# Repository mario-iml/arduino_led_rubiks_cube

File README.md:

# arduino_led_rubiks_cube
Disclaimer: This was in 2019, and we didn't even know about Git yet, so we had to scrape together Code and PCB files from old chats. We take no guarantee that this works and is up-to-date :).

## Description
Arduino based LED Rubik's Cube. 
This Project was made as a High-school Project with two other Students. To achieve this, we had to:
- Design of PCB's encompassing the buttons, LED's and shift registers with EAGLE
- Designing and Printing of the cubes case
- Assembling and Wirering the PCB's and Arduino
- Write the Code in Arduino IDE with C++

## Problems we encountered
- We were all pretty new to Computer Science and Electrical Engineering. We made many mistakes but learned many things in the process.
- We accidentally ordered the wrong type of LEDs (common anode instead of common cathode) for the PCB without realizing it. In the end, we had to desolder some of the LEDs again :(
- There were mistakes in the first version of the PCB design, which caused us to get dangerously close to the deadline due to long delivery times.

## PCB designs
The PCBs were designed with the Eagle software. Design files can be found in the Repo and here are some Screenshots:

## Other Images

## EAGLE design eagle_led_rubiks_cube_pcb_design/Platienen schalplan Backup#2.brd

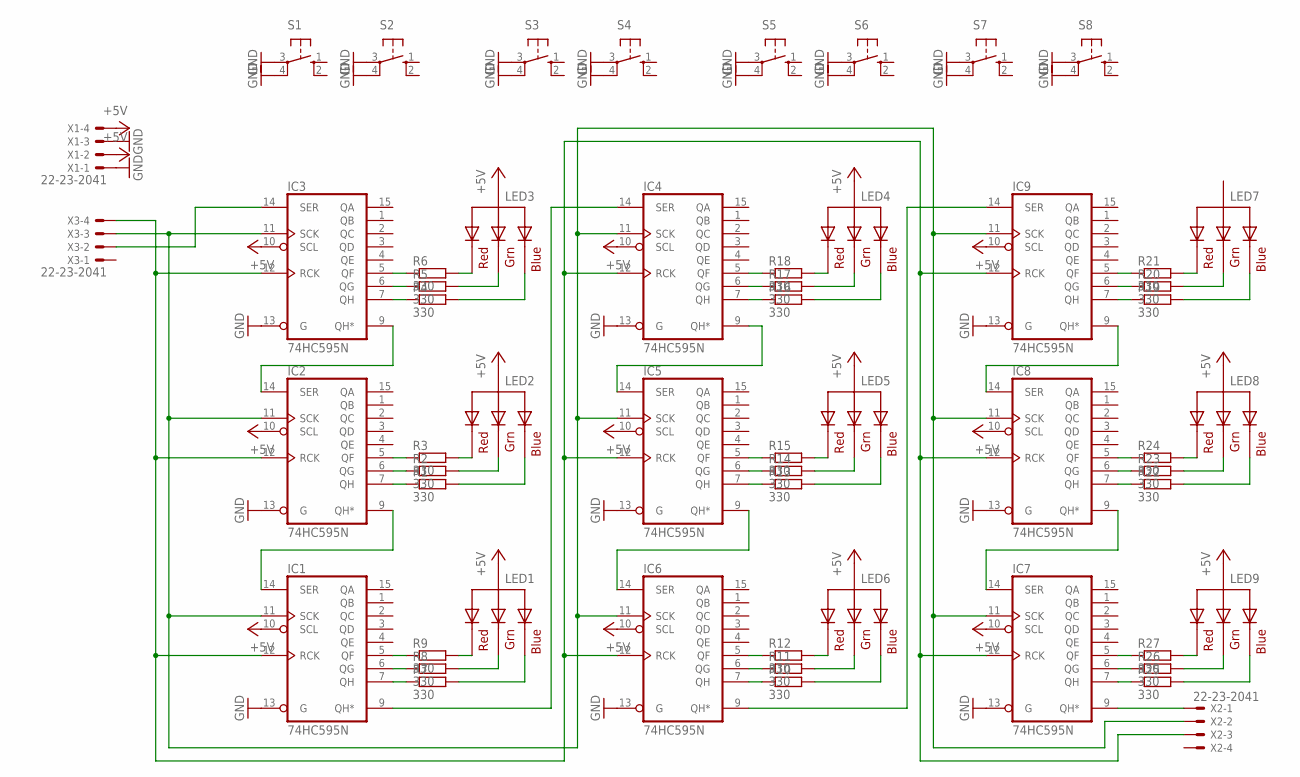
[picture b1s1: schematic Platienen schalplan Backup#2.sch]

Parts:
IC1, IC2, IC3, IC4, IC5, IC6, IC7, IC8, IC9: 74HC595N; DIL16
LED1, LED2, LED3, LED4, LED5, LED6, LED7, LED8, LED9: RGBLED_CA-5MM; LED5MMRGB
R1, R2, R3, R4, R5, R6, R7, R8, R9, R10, R11, R12, R13, R14, R15, R16, R17, R18, R19, R20, R21, R22, R23, R24, R25, R26, R27: 330; 0204/5
S1, S2, S3, S4, S5, S6, S7, S8: 10-XX; B3F-10XX
X1, X2, X3: 22-23-2041

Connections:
+5V: IC1.10 (SCL), IC2.10 (SCL), IC3.10 (SCL), IC4.10 (SCL), IC5.10 (SCL), IC6.10 (SCL), IC7.10 (SCL), IC8.10 (SCL), IC9.10 (SCL), LED1.2 (VCC), LED2.2 (VCC), LED3.2 (VCC), LED4.2 (VCC), LED5.2 (VCC), LED6.2 (VCC), LED8.2 (VCC), LED9.2 (VCC), X1.2, X1.4
GND: IC1.8 (GND), IC1.13 (G), IC2.8 (GND), IC2.13 (G), IC3.8 (GND), IC3.13 (G), IC4.8 (GND), IC4.13 (G), IC5.8 (GND), IC5.13 (G), IC6.8 (GND), IC6.13 (G), IC7.8 (GND), IC7.13 (G), IC8.8 (GND), IC8.13 (G), IC9.8 (GND), IC9.13 (G), S1.3, S1.4 (P1), S2.3, S2.4 (P1), S3.3, S3.4 (P1), S4.3, S4.4 (P1), S5.3, S5.4 (P1), S6.3, S6.4 (P1), S7.3, S7.4 (P1), S8.3, S8.4 (P1), X1.1, X1.3
unnamed: IC3.7 (QH), R4.1
unnamed: IC3.6 (QG), R5.1
unnamed: IC3.5 (QF), R6.1
unnamed: LED5.1 (RED), R15.2
unnamed: LED4.1 (RED), R18.2
unnamed: LED7.1 (RED), R21.2
unnamed: IC2.7 (QH), R1.1
unnamed: IC2.6 (QG), R2.1
unnamed: IC2.5 (QF), R3.1
unnamed: IC1.5 (QF), R9.1
unnamed: IC1.6 (QG), R8.1
unnamed: IC1.7 (QH), R7.1
unnamed: LED7.3 (GREEN), R20.2
unnamed: LED7.4 (BLUE), R19.2
unnamed: LED8.1 (RED), R24.2
unnamed: LED8.3 (GREEN), R23.2
unnamed: LED8.4 (BLUE), R22.2
unnamed: LED9.1 (RED), R27.2
unnamed: IC6.7 (QH), R10.1
unnamed: IC6.6 (QG), R11.1
unnamed: IC6.5 (QF), R12.1
unnamed: LED9.3 (GREEN), R26.2
unnamed: LED9.4 (BLUE), R25.2
unnamed: LED6.1 (RED), R12.2
unnamed: IC5.7 (QH), R13.1
unnamed: IC5.6 (QG), R14.1
unnamed: IC5.5 (QF), R15.1
unnamed: LED6.3 (GREEN), R11.2
unnamed: LED6.4 (BLUE), R10.2
unnamed: LED5.3 (GREEN), R14.2
unnamed: IC4.7 (QH), R16.1
unnamed: IC4.6 (QG), R17.1
unnamed: IC4.5 (QF), R18.1
unnamed: LED5.4 (BLUE), R13.2
unnamed: LED4.3 (GREEN), R17.2
unnamed: LED4.4 (BLUE), R16.2
unnamed: IC9.7 (QH), R19.1
unnamed: IC9.6 (QG), R20.1
unnamed: IC9.5 (QF), R21.1
unnamed: IC8.5 (QF), R24.1
unnamed: IC8.6 (QG), R23.1
unnamed: IC8.7 (QH), R22.1
unnamed: IC7.5 (QF), R27.1
unnamed: IC7.6 (QG), R26.1
unnamed: IC7.7 (QH), R25.1
unnamed: LED2.1 (RED), R3.2
unnamed: LED2.3 (GREEN), R2.2
unnamed: LED2.4 (BLUE), R1.2
unnamed: LED1.1 (RED), R9.2
unnamed: LED1.3 (GREEN), R8.2
unnamed: LED1.4 (BLUE), R7.2
unnamed: LED3.1 (RED), R6.2
unnamed: LED3.3 (GREEN), R5.2
unnamed: IC2.14 (SER), IC3.9 (QH*)
unnamed: IC1.14 (SER), IC2.9 (QH*)
unnamed: IC1.9 (QH*), IC4.14 (SER)
unnamed: IC4.9 (QH*), IC5.14 (SER)
unnamed: IC5.9 (QH*), IC6.14 (SER)
unnamed: IC6.9 (QH*), IC9.14 (SER)
unnamed: IC8.14 (SER), IC9.9 (QH*)
unnamed: IC7.14 (SER), IC8.9 (QH*)
unnamed: IC1.12 (RCK), IC2.12 (RCK), IC3.12 (RCK), IC4.12 (RCK), IC5.12 (RCK), IC6.12 (RCK), IC7.12 (RCK), IC8.12 (RCK), IC9.12 (RCK), X2.3, X3.4
unnamed: IC3.14 (SER), X3.2
unnamed: IC1.11 (SCK), IC2.11 (SCK), IC3.11 (SCK), IC4.11 (SCK), IC5.11 (SCK), IC6.11 (SCK), IC7.11 (SCK), IC8.11 (SCK), IC9.11 (SCK), X2.2, X3.3
unnamed: IC7.9 (QH*), X2.1
unnamed: LED3.4 (BLUE), R4.2
VCC: IC1.16 (VCC), IC2.16 (VCC), IC3.16 (VCC), IC4.16 (VCC), IC5.16 (VCC), IC6.16 (VCC), IC7.16 (VCC), IC8.16 (VCC), IC9.16 (VCC)

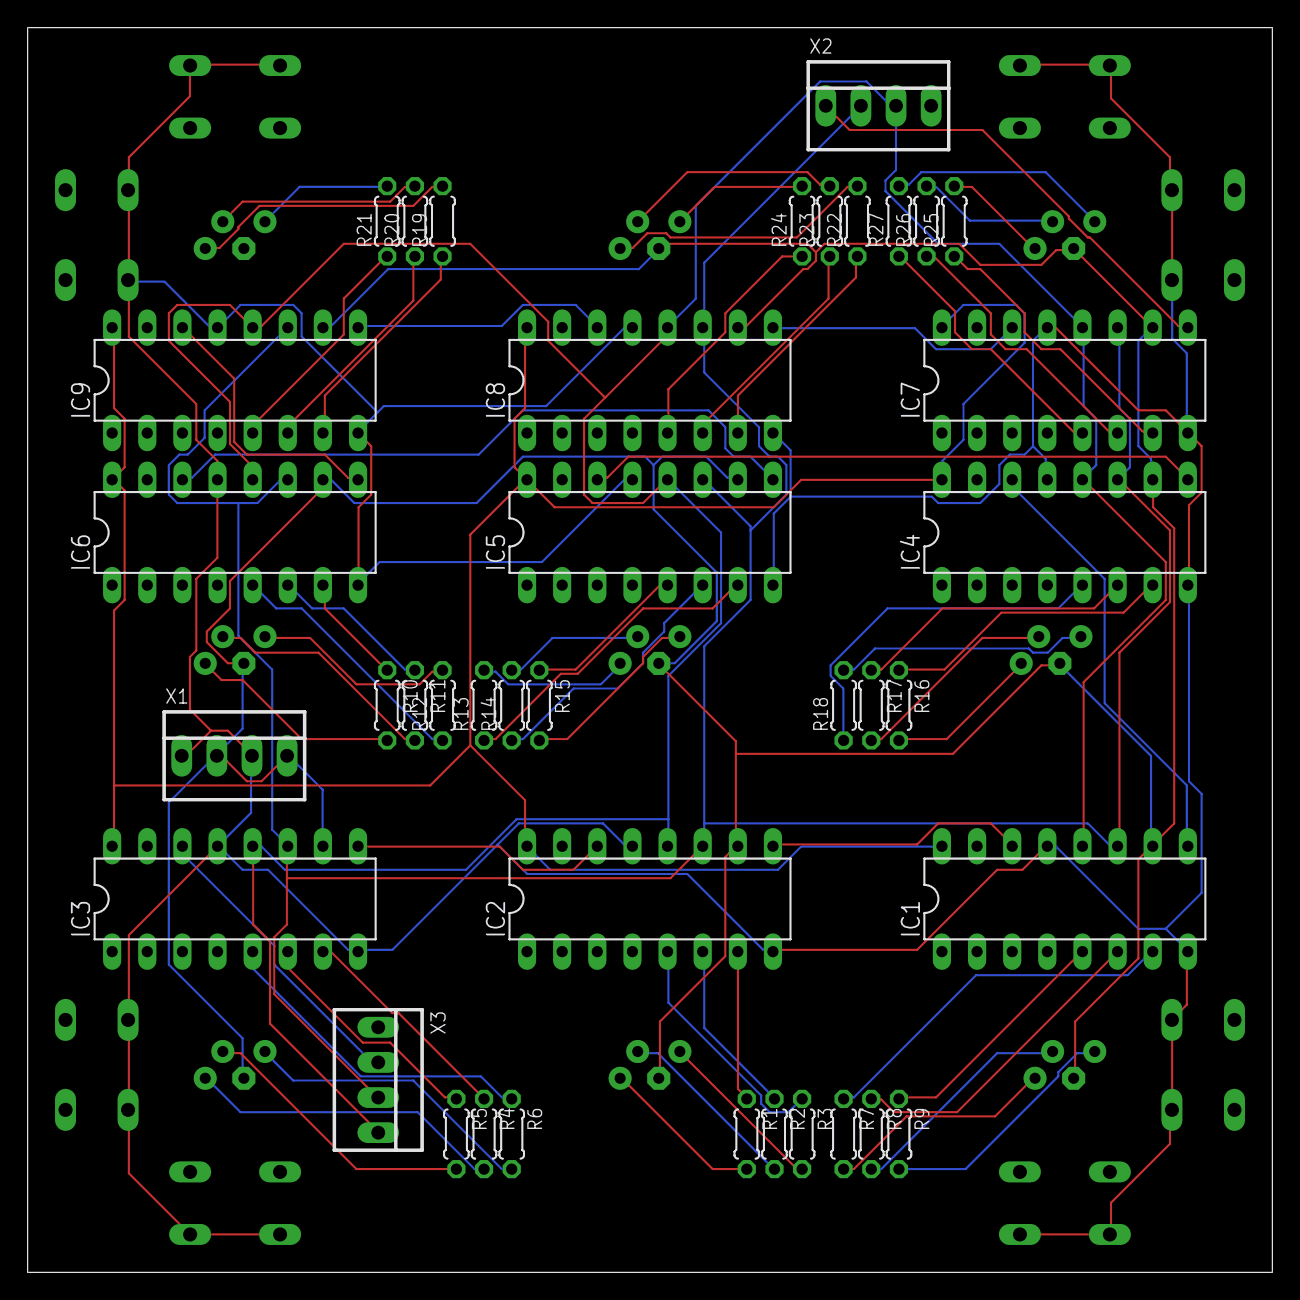
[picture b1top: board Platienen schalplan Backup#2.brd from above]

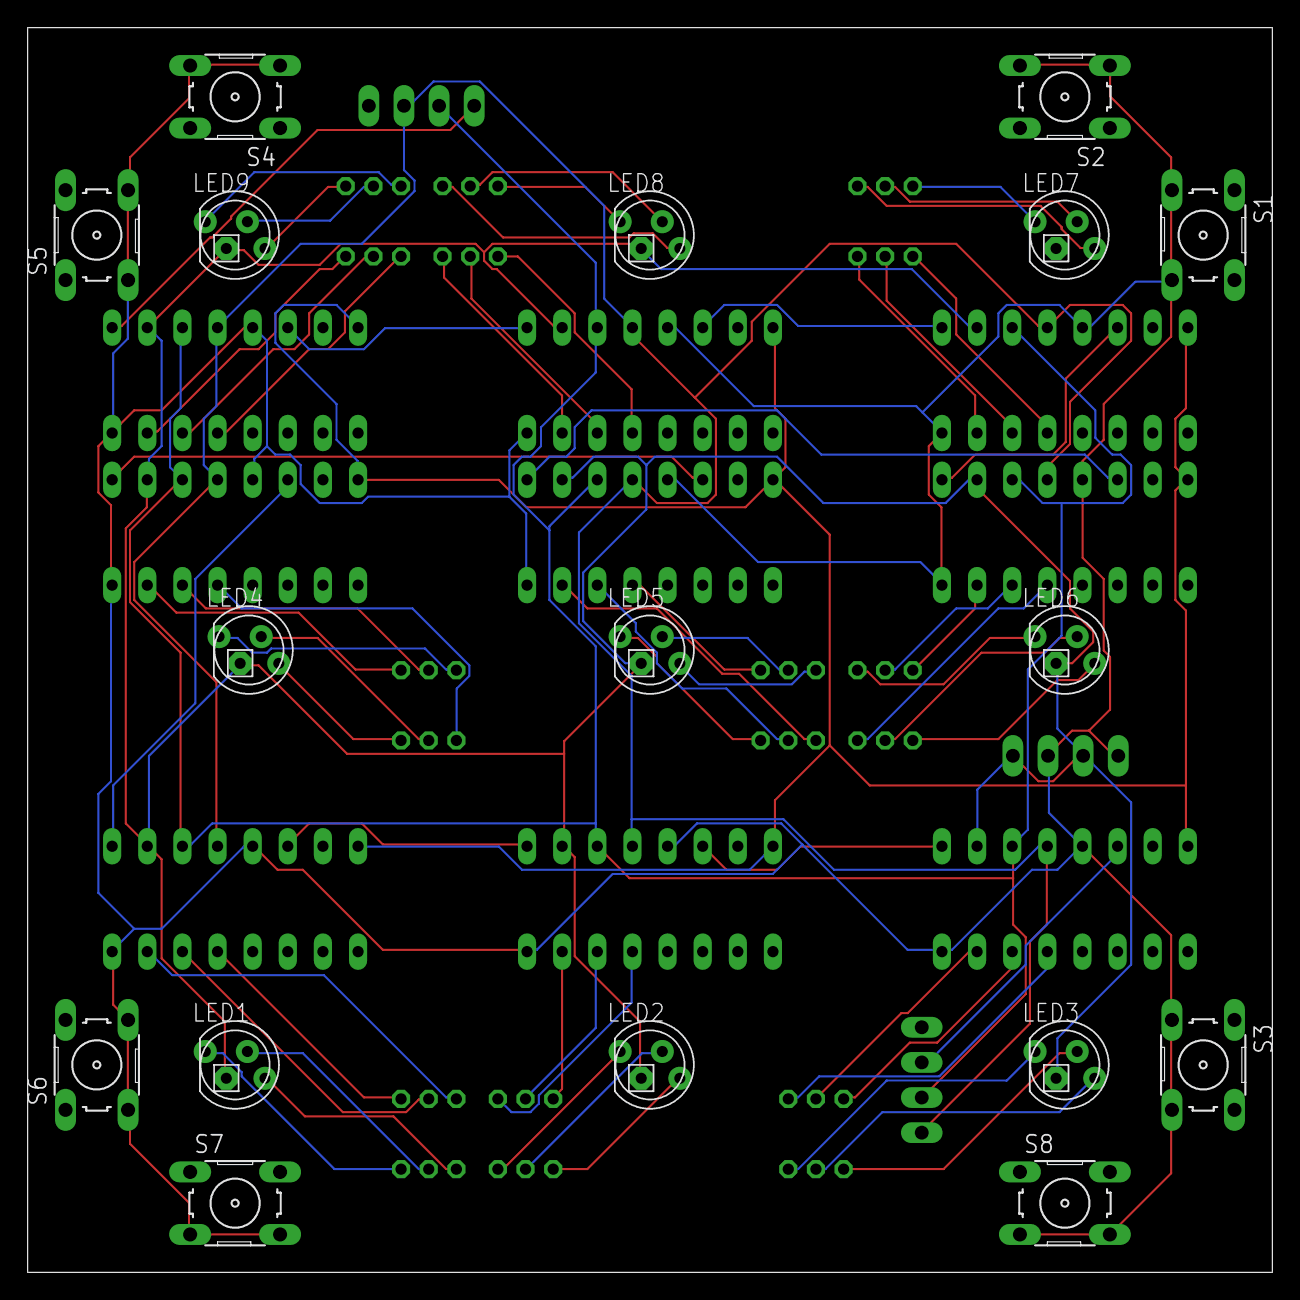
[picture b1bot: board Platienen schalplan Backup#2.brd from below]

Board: 2 copper layers, 90.0 x 90.0 mm, 56 parts (17 on the bottom side), 69 nets.

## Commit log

2025-11-13 Update README with project details and images
    Added detailed project description, problems encountered, and PCB design information.
2025-11-13 Update images in README.md
    Removed two images and added a new image in the README.
2025-11-13 adding pcb design files and part of the code we could recover. NOT COMPLETE
